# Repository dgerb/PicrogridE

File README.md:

# PicrogridEducational
Repository for Picrogrid Raspberry Pi code and scripts and Atverter Arduino code

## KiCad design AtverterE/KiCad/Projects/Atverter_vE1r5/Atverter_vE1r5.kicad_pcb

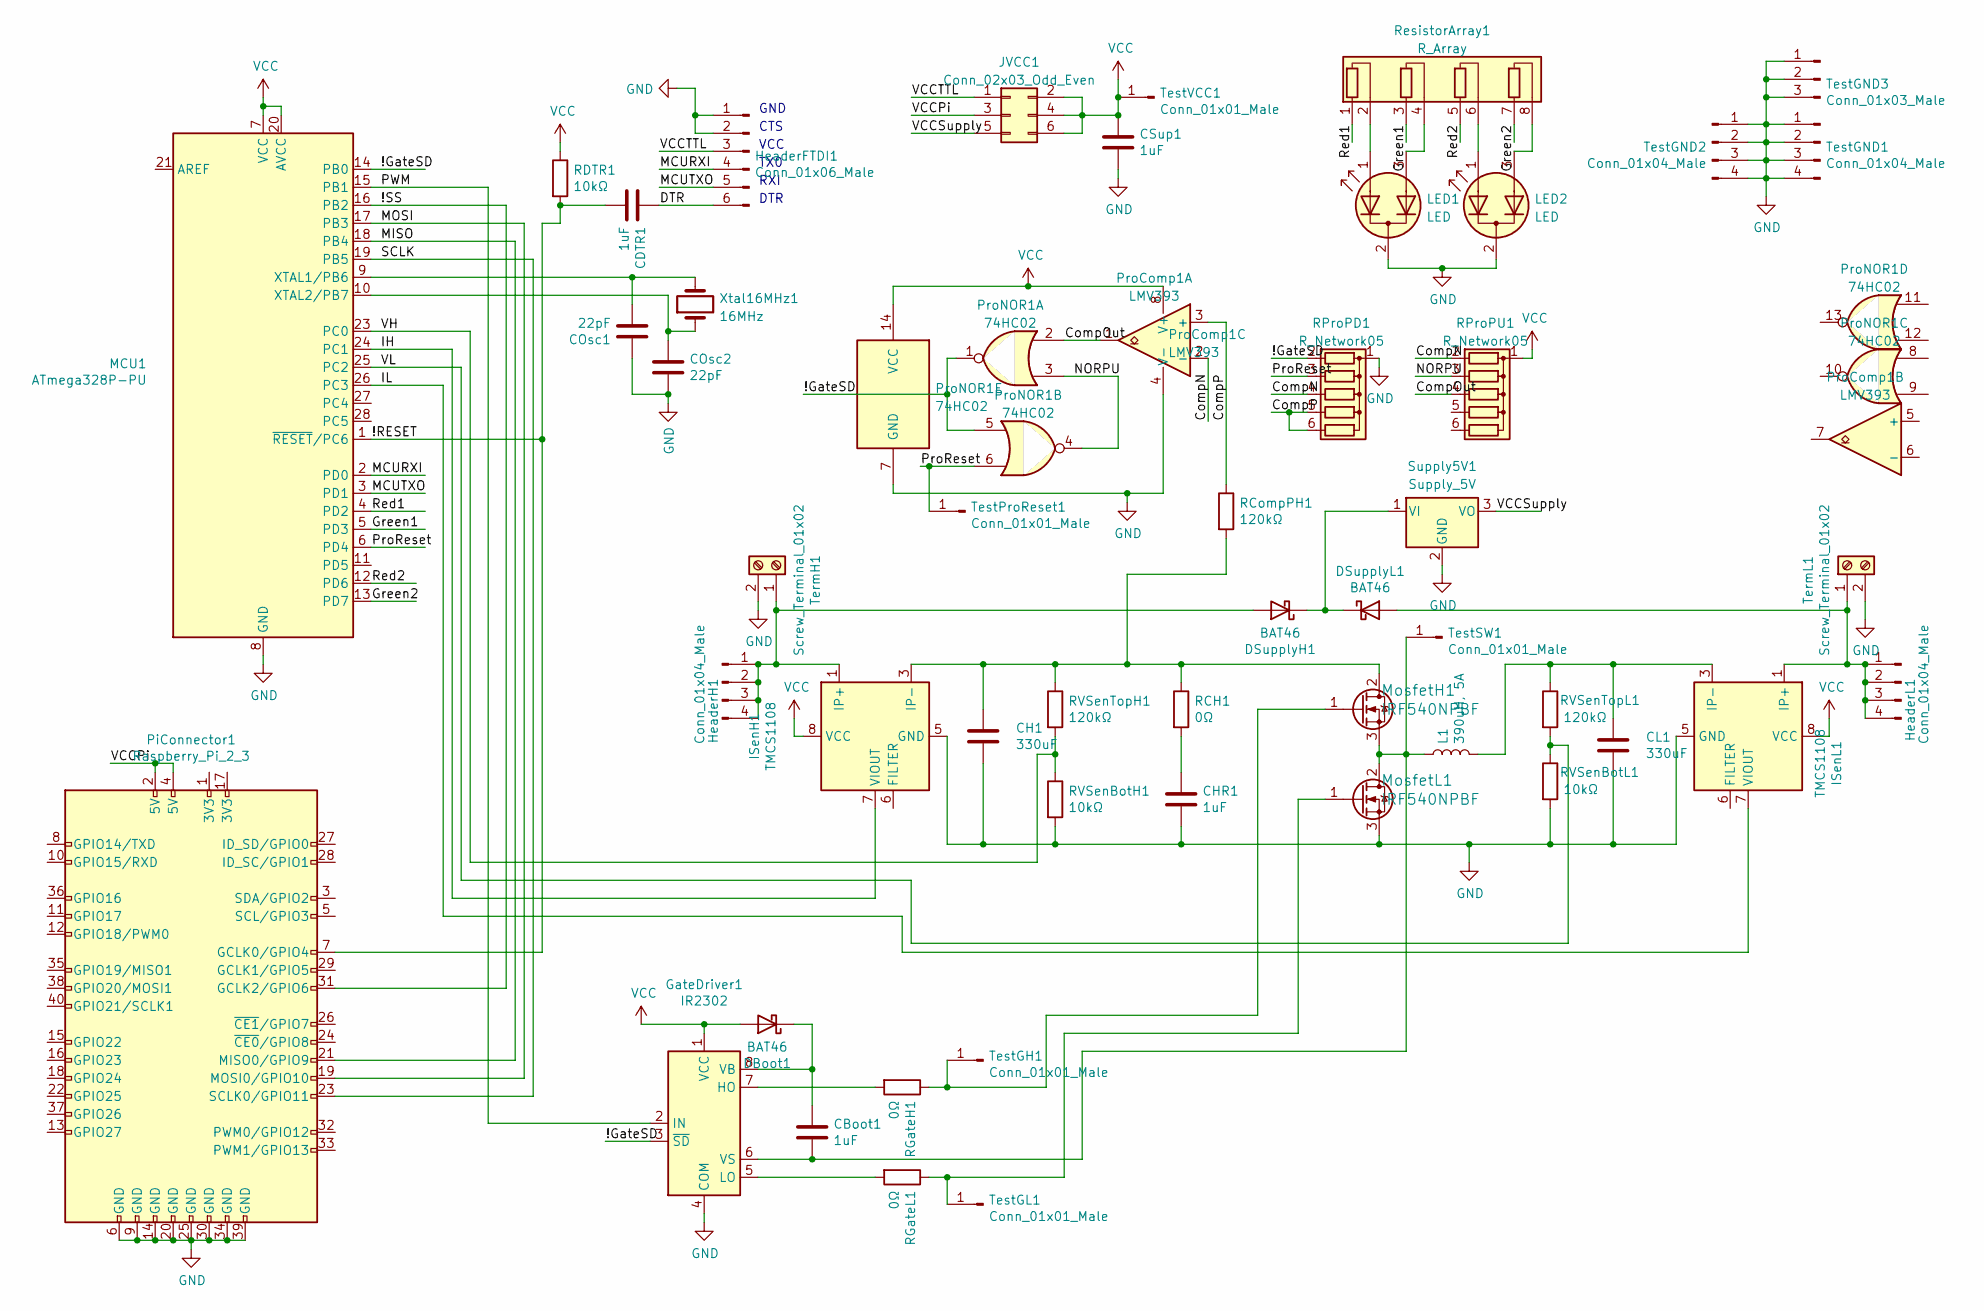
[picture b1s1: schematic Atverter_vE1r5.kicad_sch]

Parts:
CBoot1: 1uF; C_Rect_L7.2mm_W3.5mm_P5.00mm_FKS2_FKP2_MKS2_MKP2
CDTR1: 1uF; C_Rect_L7.2mm_W3.5mm_P5.00mm_FKS2_FKP2_MKS2_MKP2
CH1: 330uF; CP_Radial_D18.0mm_P7.50mm
CHR1: 1uF; C_Rect_L7.2mm_W3.5mm_P5.00mm_FKS2_FKP2_MKS2_MKP2
CL1: 330uF; CP_Radial_D18.0mm_P7.50mm
COsc1, COsc2: 22pF; C_Rect_L7.2mm_W3.5mm_P5.00mm_FKS2_FKP2_MKS2_MKP2
CSup1: 1uF; C_Rect_L7.2mm_W3.5mm_P5.00mm_FKS2_FKP2_MKS2_MKP2
DBoot1: BAT46; D_DO-35_SOD27_P7.62mm_Horizontal
DSupplyH1: BAT46; D_DO-35_SOD27_P7.62mm_Horizontal
DSupplyL1: BAT46; D_DO-35_SOD27_P7.62mm_Horizontal
GateDriver1: IR2302; DIP-8_W7.62mm_LongPads
HeaderFTDI1: Conn_01x06_Male; FTDI_USB_TTL_Header
HeaderH1: Conn_01x04_Male; PinHeader_1x04_P2.54mm_Vertical
HeaderL1: Conn_01x04_Male; PinHeader_1x04_P2.54mm_Vertical
ISenH1: TMCS1108; SOIC-8_3.9x4.9mm_P1.27mm
ISenL1: TMCS1108; SOIC-8_3.9x4.9mm_P1.27mm
JVCC1: Conn_02x03_Odd_Even; PinHeader_2x03_P2.54mm_Vertical
L1: 390uH, 5A; L_Toroid_Horizontal_D32.5mm_P30.00mm_Bourns_2300
LED1, LED2: LED; LED_3pin_P2.54mm
MCU1: ATmega328P-PU; DIP-28_W7.62mm
MosfetH1: IRF540NPBF; TO-220-3_Vertical; MPN IRF540NPBF; Digi-Key_PN IRF540NPBF-ND
MosfetL1: IRF540NPBF; TO-220-3_Vertical; MPN IRF540NPBF; Digi-Key_PN IRF540NPBF-ND
PiConnector1: Raspberry_Pi_2_3; Raspberry_Pi_Zero_and_Four
ProComp1: LMV393; DIP-8_W7.62mm_LongPads
ProNOR1: 74HC02; DIP-14_W7.62mm_LongPads
RCH1: 0Ω; R_Axial_DIN0207_L6.3mm_D2.5mm_P7.62mm_Horizontal
RCompPH1: 120kΩ; R_Axial_DIN0207_L6.3mm_D2.5mm_P7.62mm_Horizontal
RDTR1: 10kΩ; R_Axial_DIN0207_L6.3mm_D2.5mm_P7.62mm_Horizontal
RGateH1: 0Ω; R_Axial_DIN0207_L6.3mm_D2.5mm_P7.62mm_Horizontal
RGateL1: 0Ω; R_Axial_DIN0207_L6.3mm_D2.5mm_P7.62mm_Horizontal
RProPD1: R_Network05; R_Array_SIP6
RProPU1: R_Network05; R_Array_SIP6
RVSenBotH1: 10kΩ; R_Axial_DIN0207_L6.3mm_D2.5mm_P7.62mm_Horizontal
RVSenBotL1: 10kΩ; R_Axial_DIN0207_L6.3mm_D2.5mm_P7.62mm_Horizontal
RVSenTopH1: 120kΩ; R_Axial_DIN0207_L6.3mm_D2.5mm_P7.62mm_Horizontal
RVSenTopL1: 120kΩ; R_Axial_DIN0207_L6.3mm_D2.5mm_P7.62mm_Horizontal
ResistorArray1: R_Array; R_Array_SIP8
Supply5V1: Supply_5V; SupplyDC_48V-5V_TO-220-3_Vertical
TermH1: Screw_Terminal_01x02; Term_Block_1x2_P5mm
TermL1: Screw_Terminal_01x02; Term_Block_1x2_P5mm
TestGH1: Conn_01x01_Male; PinHeader_1x01_P2.54mm_Vertical
TestGL1: Conn_01x01_Male; PinHeader_1x01_P2.54mm_Vertical
TestGND1, TestGND2: Conn_01x04_Male; PinHeader_1x04_P2.54mm_Vertical
TestGND3: Conn_01x03_Male; PinHeader_1x03_P2.54mm_Vertical
TestProReset1: Conn_01x01_Male; PinHeader_1x01_P2.54mm_Vertical
TestSW1: Conn_01x01_Male; PinHeader_1x01_P2.54mm_Vertical
TestVCC1: Conn_01x01_Male; PinHeader_1x01_P2.54mm_Vertical
Xtal16MHz1: 16MHz; Resonator-2Pin_W10.0mm_H5.0mm

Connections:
/!GateSD: GateDriver1.3 (~SD), MCU1.14 (PB0), ProNOR1.1, ProNOR1.5, RProPD1.2 (R1)
/!RESET: CDTR1.2, MCU1.1 (~RESET/PC6), PiConnector1.7 (GCLK0/GPIO4), RDTR1.2
/!SS: MCU1.16 (PB2), PiConnector1.31 (GCLK2/GPIO6)
/CompN: ProComp1.2 (-), RProPD1.4 (R3), RProPU1.2 (R1)
/CompOut: ProComp1.1, ProNOR1.2, RProPU1.4 (R3)
/CompP: ProComp1.3 (+), RCompPH1.1, RProPD1.5 (R4), RProPD1.6 (R5); also elsewhere on the board
/DTR: CDTR1.1, HeaderFTDI1.6
/Green1: MCU1.5 (PD3), ResistorArray1.3 (R2.1)
/Green2: MCU1.13 (PD7), ResistorArray1.7 (R4.1)
/IH: ISenH1.7 (VIOUT), MCU1.24 (PC1)
/IL: ISenL1.7 (VIOUT), MCU1.26 (PC3)
/MCURXI: HeaderFTDI1.4, MCU1.2 (PD0)
/MCUTXO: HeaderFTDI1.5, MCU1.3 (PD1)
/MISO: MCU1.18 (PB4), PiConnector1.21 (MISO0/GPIO9)
/MOSI: MCU1.17 (PB3), PiConnector1.19 (MOSI0/GPIO10)
/NORPU: ProNOR1.3, ProNOR1.4, RProPU1.3 (R2)
/PWM: GateDriver1.2 (IN), MCU1.15 (PB1)
/ProReset: MCU1.6 (PD4), ProNOR1.6, RProPD1.3 (R2), TestProReset1.1
/Red1: MCU1.4 (PD2), ResistorArray1.1 (R1.1)
/Red2: MCU1.12 (PD6), ResistorArray1.5 (R3.1)
/SCLK: MCU1.19 (PB5), PiConnector1.23 (SCLK0/GPIO11)
/VCCPi: JVCC1.3, PiConnector1.2 (5V), PiConnector1.4 (5V)
/VCCSupply: JVCC1.5, Supply5V1.3 (VO)
/VCCTTL: HeaderFTDI1.3, JVCC1.1
/VH: MCU1.23 (PC0), RVSenBotH1.1, RVSenTopH1.2
/VL: MCU1.25 (PC2), RVSenBotL1.1, RVSenTopL1.2
GND: CH1.2, CHR1.2, CL1.2, COsc1.1, COsc2.2, CSup1.2, GateDriver1.4 (COM), HeaderFTDI1.1, HeaderFTDI1.2, ISenH1.5 (GND), ISenL1.5 (GND), LED1.2 (K), LED2.2 (K), MCU1.8 (GND), MCU1.22 (GND), MosfetL1.3 (S), PiConnector1.6 (GND), PiConnector1.9 (GND), PiConnector1.14 (GND), PiConnector1.20 (GND), PiConnector1.25 (GND), PiConnector1.30 (GND), PiConnector1.34 (GND), PiConnector1.39 (GND), ProComp1.4 (V-), ProNOR1.7 (GND), RProPD1.1 (common), RVSenBotH1.2, RVSenBotL1.2, Supply5V1.2 (GND), TermH1.2, TermL1.2, TestGND1.1, TestGND1.2, TestGND1.3, TestGND1.4, TestGND2.1, TestGND2.2, TestGND2.3, TestGND2.4, TestGND3.1, TestGND3.2, TestGND3.3
unnamed: CBoot1.1, DBoot1.1 (K), GateDriver1.8 (VB)
unnamed: CBoot1.2, GateDriver1.6 (VS), L1.1, MosfetH1.3 (S), MosfetL1.2 (D), TestSW1.1
unnamed 29: CH1.1, ISenH1.3 (IP-), ISenH1.4 (IP-), MosfetH1.2 (D), RCH1.1, RCompPH1.2, RVSenTopH1.1; also elsewhere on the board
unnamed: CHR1.1, RCH1.2
unnamed: CL1.1, ISenL1.3 (IP-), ISenL1.4 (IP-), L1.2, RVSenTopL1.1
unnamed: COsc1.2, MCU1.9 (XTAL1/PB6), Xtal16MHz1.2
unnamed: COsc2.1, MCU1.10 (XTAL2/PB7), Xtal16MHz1.1
unnamed: DSupplyH1.1 (K), DSupplyL1.1 (K), Supply5V1.1 (VI)
unnamed: DSupplyH1.2 (A), HeaderH1.1, HeaderH1.2, HeaderH1.3, HeaderH1.4, ISenH1.1 (IP+), ISenH1.2 (IP+), TermH1.1
unnamed: DSupplyL1.2 (A), HeaderL1.1, HeaderL1.2, HeaderL1.3, HeaderL1.4, ISenL1.1 (IP+), ISenL1.2 (IP+), TermL1.1
unnamed: GateDriver1.5 (LO), RGateL1.2
unnamed: GateDriver1.7 (HO), RGateH1.2
unnamed: LED1.1 (A1), ResistorArray1.2 (R1.2)
unnamed: LED1.3 (A2), ResistorArray1.4 (R2.2)
unnamed: LED2.1 (A1), ResistorArray1.6 (R3.2)
unnamed: LED2.3 (A2), ResistorArray1.8 (R4.2)
unnamed: MosfetH1.1 (G), RGateH1.1, TestGH1.1
unnamed: MosfetL1.1 (G), RGateL1.1, TestGL1.1
VCC: CSup1.1, DBoot1.2 (A), GateDriver1.1 (VCC), ISenH1.8 (VCC), ISenL1.8 (VCC), JVCC1.2, JVCC1.4, JVCC1.6, MCU1.7 (VCC), MCU1.20 (AVCC), ProComp1.8 (V+), ProNOR1.14 (VCC), RDTR1.1, RProPU1.1 (common), TestVCC1.1

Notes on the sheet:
RXI
GND
VCC
TX0
DTR
CTS

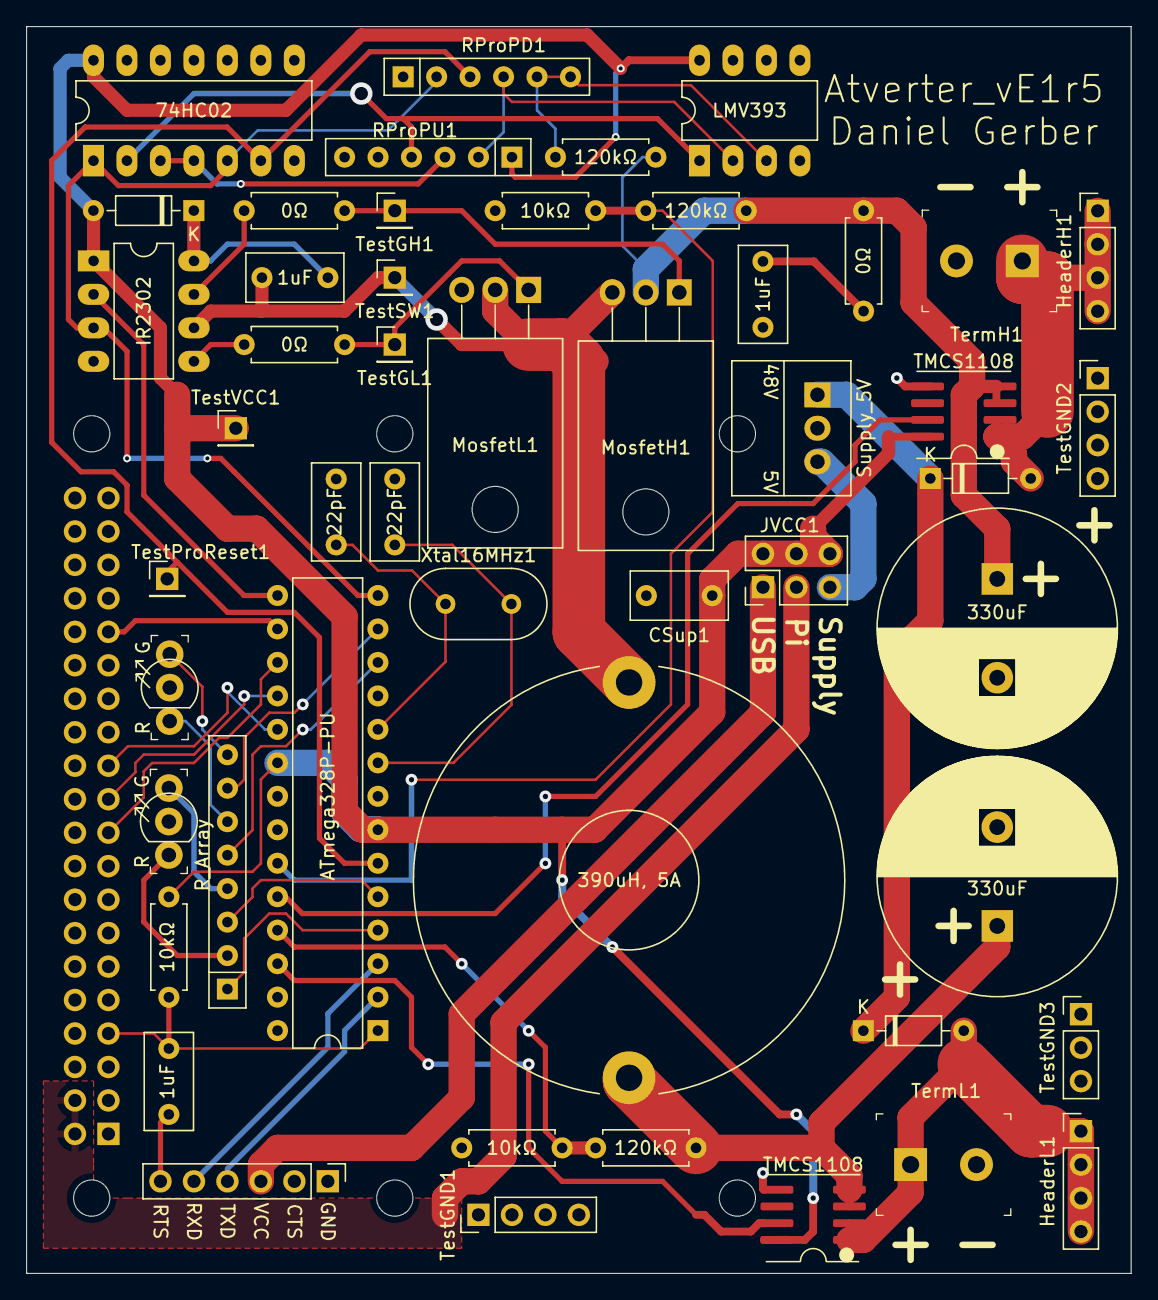
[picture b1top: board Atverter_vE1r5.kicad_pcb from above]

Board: 2 copper layers, 83.8 x 94.6 mm, 51 parts (1 on the bottom side), 46 nets.

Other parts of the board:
locked: 120kΩ; R_Axial_DIN0207_L6.3mm_D2.5mm_P7.62mm_Horizontal

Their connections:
/CompP: locked.1; also elsewhere on the board
unnamed 29: locked.2; also elsewhere on the board

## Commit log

2022-09-15 created set up readme
2022-09-15 update setup readme and singlepisetup and atvertersetup
2022-09-15 finalized setup
2022-09-15 updated atverter setup
2022-09-20 starting library and blink example
2022-09-21 added PWM, pro reset, untested vh ih vl il, PWMTest example
2022-09-21 better documentation for flashing atverter
2022-10-04 added KiCad PCB v1r4
2022-10-17 added kicad files for Atverter_vE1r5, cleaned up library
2022-11-16 added digikey BOM
2023-01-26 Current and Voltage Control Code
2023-01-27 Fixed Compile error
    Line 32 added parenthesis to properly call function
2023-02-02 Current Controller
    Updated Current Controller and started Battery charging and voltage controller (Boost)
2023-02-08 Updated Voltage Controller
    Added Smoothing controls to maintain output voltage when desired value is pinpointed
2023-02-15 Updated Voltage_Controller_Buck
    Added Some more smoothing controller but still need to fix and add in a moving average to made the smoothing controller better
2023-02-22 Added averaging filter
2023-03-03 Buck Controller update
    - Refactored the code to make it more modular and readable
    - Implemented error equation to jump to correct duty cycle
    - Implemented moving average filter to maintain steady output voltage
    - Refactored code can now sample at 1ms
2023-03-06 Buck Voltage control and Buck Current control
    Added calibration to the buck controller
    Current controller a better plan is needed to smooth out the output
2023-03-09 Voltage controller and current controller fixes
2023-03-09 Sensor Characterization added
    Added test file to characterize the voltage and current sensors
2023-03-09 Finished updating voltage sensors
2023-03-09 Updated Voltage Controller Buck
    Added the sensor fixes
2023-03-15 Voltage Controller, Current Controller, and Sensor Additions
    Voltage Controller_Buck: Finished Tweaking it
    Current Controller: Code finished but needs some tweaking and more sensor characterization so it works across many voltages.
2023-04-12 Voltage Controller Buck and current controller fixes
    Made the voltage controller more of a critically damped oscillator (less ringing).
    Current controller: Finalized the characteristics of the current controller. Code for actual current controller doesn't work at the moment. Resolution is strange and the jumps in current values is a 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
2023-04-20 Current and Voltage fixes
2023-04-26 Voltage Controller Boost code started
    Battery_Charging: Now that current and voltage controllers done can focus on adding to battery charge code
    Current and voltage controllers tweaked a bit and added sensor data for second atverterE board
    Voltage controller boost: started this code needs some others eyes to look at but idea works so far but very jumpy
2023-05-03 deleted some files
2023-05-03 Create atverter_flow.json
    added node red file
2023-05-03 Some changes
    Not permanent, attempting to convert .ino files to h and cpp files but struggling at moment
2023-05-04 header and source file for voltage controller
2023-05-11 Some corrections
2023-05-11 changed main.ino. uncommented initializeinterrupstimer in the library files
2023-05-11 Boost fixes
2023-05-16 stuff
2023-05-18 added an if statement in boost controll main
2023-05-25 Added PI controller to Boost and Buck and Main
2023-05-25 Added PI control to Main file as well as current control and buck individually
    Still have to add current contorl to the Main file
2023-05-29 Updated flows and changed main
2023-05-29 added current control state but no logic yet
2023-05-29 Update Buck control system
    Captured pictures and added steady state error
2023-05-31 Final updates
    Characterized last Atverter sensors
    Updated flow for server
    Added current control to main file
2023-06-03 Got rid of some comments and simple tuning adjustments
2023-06-23 Upload with two paths to output
    Some comments contain a method for determining the current the atverter should be drawing. Those current numbers are not necessary to determine output bit code, but can be uncommented to match curren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
2023-06-23 initial commit
    RPi version of the output sim. Tested and validated.
2023-06-26 Added JSON file functionality
    data will be inputted to the system as a JSON file. Program reads price data and uses it when calculating binary signals.
2023-06-26 added JSON functionality and changed GPIO pin
2023-06-26 Initial Commit: Testing JSON price data
2023-07-03 output_signals with serial capability
2023-07-03 Arduino serial code to go with serial_testing
    for sim only
2023-07-06 Simplified binary mapping, program now outputs integers
2023-07-06 simplified binary and added bidirectional serial
2023-07-06 added comments
2023-07-06 fixed indentation
2023-07-26 added comments, removed unnecessary libraries
2023-08-03 finalized PWM constraints
2023-08-04 Included serial command input
2023-08-04 hex file upload
